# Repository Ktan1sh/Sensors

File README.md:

# Sensor Breakout Boards

These are some Sensor breakout boards I created for practicing PCB design and Git version control.

## Purpose

- Hone my Design skills
- Practice Git workflows for hardware or software projects.
- Build reusable modules for future projects.

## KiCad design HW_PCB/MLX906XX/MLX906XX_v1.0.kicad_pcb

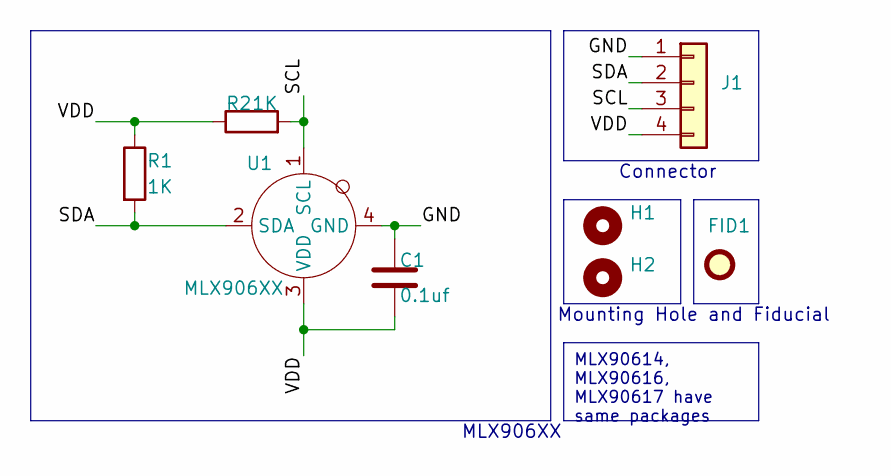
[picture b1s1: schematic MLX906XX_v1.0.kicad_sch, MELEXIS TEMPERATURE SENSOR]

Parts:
C1: 0.1uf; C_0603_1608Metric_Pad1.08x0.95mm_HandSolder
FID1: Fiducial; Fiducial_0.5mm_Mask1.5mm
H1, H2: MountingHole; MountingHole_3.2mm_M3
J1: Conn_01x04; PinSocket_1x04_P2.54mm_Horizontal
R1, R2: 1K; R_0603_1608Metric_Pad0.98x0.95mm_HandSolder
U1: MLX906XX; MLX906XX_TO39

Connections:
GND: C1.1, J1.1, U1.4 (GND)
SCL: J1.3, R2.2, U1.1 (SCL)
SDA: J1.2, R1.2, U1.2 (SDA)
VDD: C1.2, J1.4, R1.1, R2.1, U1.3 (VDD)

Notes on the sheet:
MLX90614, MLX90616, MLX90617 have same packages
Mounting Hole and Fiducial
Connector
MLX906XX

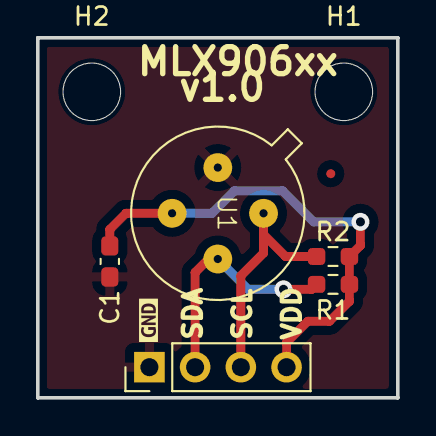
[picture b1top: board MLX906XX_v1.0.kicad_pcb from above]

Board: 2 copper layers, 20.0 x 20.0 mm, 10 parts (1 on the bottom side), 4 nets.

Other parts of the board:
kibuzzard-6799FD48, kibuzzard-6799FD48#2: G***; kibuzzard-6799FD48

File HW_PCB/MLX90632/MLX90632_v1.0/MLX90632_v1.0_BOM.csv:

"Reference","Value","Qty","DNP","MPN","Package","Description"
"C1","10n","1","","","0603","Unpolarized capacitor"
"J1","Conn_01x04","1","","","2.54 mm","Generic connector, single row, 01x04"
"R1,R2","1K","2","","","0603","Resistor"
"U1","MLX90632","1","","","5-SFN",""

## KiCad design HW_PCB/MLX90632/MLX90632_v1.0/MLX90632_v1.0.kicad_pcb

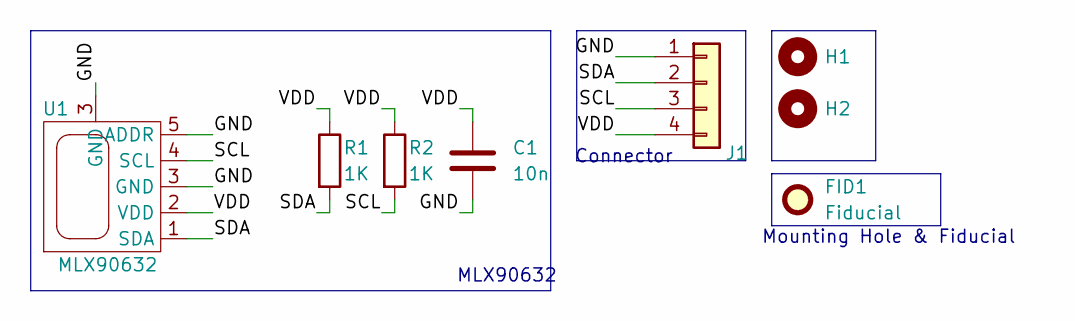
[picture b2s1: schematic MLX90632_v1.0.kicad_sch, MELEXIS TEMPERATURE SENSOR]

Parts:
C1: 10n; C_0603_1608Metric_Pad1.08x0.95mm_HandSolder
FID1: Fiducial; Fiducial_0.5mm_Mask1.5mm
H1, H2: MountingHole; MountingHole_3.2mm_M3
J1: Conn_01x04; PinHeader_1x04_P2.54mm_Vertical
R1, R2: 1K; R_0603_1608Metric_Pad0.98x0.95mm_HandSolder
U1: MLX90632; IC_MLX90632SLD-BCB-000-RE

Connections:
/GND: C1.2, J1.1, U1.3 (GND), U1.5 (ADDR)
/SCL: J1.3, R2.2, U1.4 (SCL)
/SDA: J1.2, R1.2, U1.1 (SDA)
/VDD: C1.1, J1.4, R1.1, R2.1, U1.2 (VDD)

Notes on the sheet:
MLX90632
Connector
Mounting Hole & Fiducial

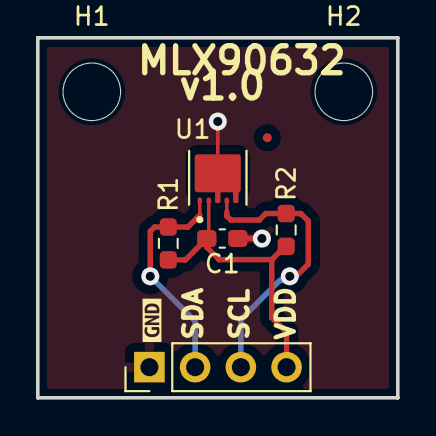
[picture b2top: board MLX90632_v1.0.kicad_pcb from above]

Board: 2 copper layers, 20.0 x 20.0 mm, 10 parts (1 on the bottom side), 4 nets.

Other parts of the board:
kibuzzard-679A3272, kibuzzard-679A3272#2: G***; kibuzzard-679A3272

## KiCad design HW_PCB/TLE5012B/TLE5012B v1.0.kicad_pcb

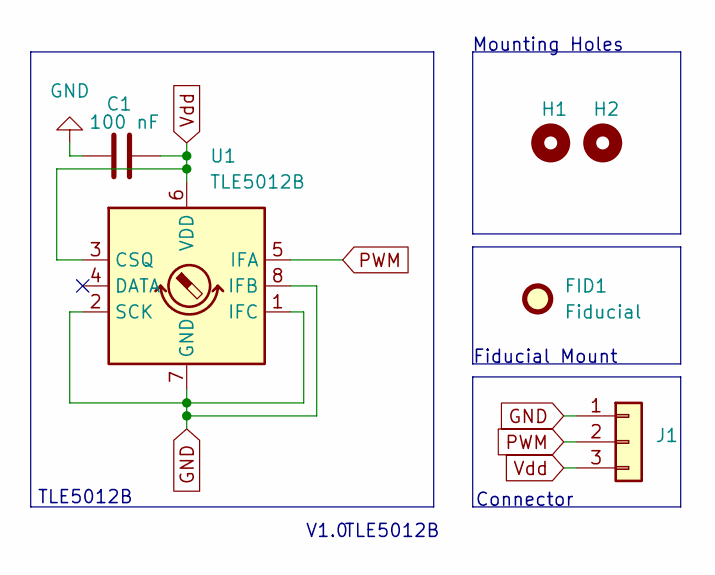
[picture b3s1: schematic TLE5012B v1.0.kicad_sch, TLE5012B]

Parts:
C1: 100 nF; C_0603_1608Metric
FID1: Fiducial; Fiducial_0.75mm_Mask2.25mm
H1, H2: MountingHole_Pad; MountingHole_3.2mm_M3
J1: PinHeader_1x03_P2.54mm_Vertical; Part Number 1-0301FBV0T
U1: TLE5012B; SOIC-8_3.9x4.9mm_P1.27mm

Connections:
GND: C1.1, J1.1, U1.1 (IFC), U1.2 (SCK), U1.7 (GND), U1.8 (IFB)
PWM: J1.2, U1.5 (IFA)
Vdd: C1.2, J1.3, U1.3 (CSQ), U1.6 (VDD)

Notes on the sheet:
TLE5012B
Mounting Holes
Connector
Fiducial Mount
V1.0

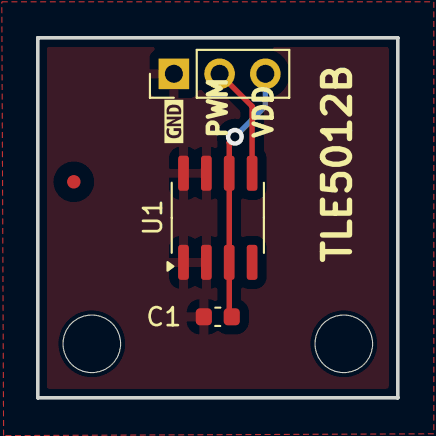
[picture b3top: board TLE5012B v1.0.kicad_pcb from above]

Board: 2 copper layers, 20.0 x 20.0 mm, 8 parts (1 on the bottom side), 3 nets.

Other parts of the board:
kibuzzard-677E552E, kibuzzard-677E552E#2: G***; kibuzzard-677E552E

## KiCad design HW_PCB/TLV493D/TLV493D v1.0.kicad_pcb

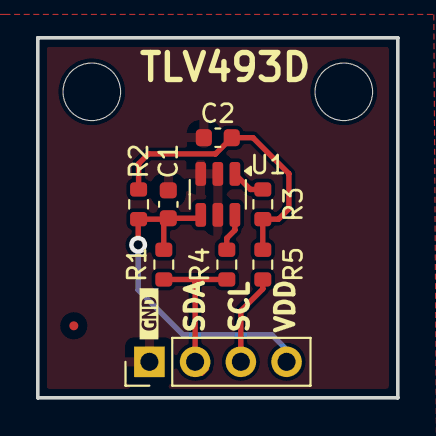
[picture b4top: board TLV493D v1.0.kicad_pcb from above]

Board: 2 copper layers, 20.0 x 20.0 mm, 14 parts (1 on the bottom side), 7 nets.

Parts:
C1: 100 nF; C_0603_1608Metric
C2: 200 pF; C_0603_1608Metric
FID2: Fiducial; Fiducial_0.5mm_Mask1.5mm
H3, H4: MountingHole_Pad; MountingHole_3.2mm_M3
J1: PinHeader_1x04_P2.54mm_Vertical
R1, R2: 1.2K; R_0603_1608Metric
R3, R4, R5: 100E; R_0603_1608Metric
U1: TLV493D; SOT-23-6
kibuzzard-67922AA7: G***; kibuzzard-67922AA7
kibuzzard-679229DC: G***; kibuzzard-679229DC

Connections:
GND: C1.2, C2.2, J1.1, U1.2 (GND), U1.3 (GND), U1.5 (GND)
unnamed: C2.1, R2.2, R3.1, R5.2
unnamed: R3.2, U1.1 (SCL/INT)
unnamed: R4.2, U1.6 (SDA/ADDR)
SCL: J1.3, R5.1
SDA: J1.2, R1.2, R4.1
Vdd: C1.1, J1.4, R1.1, R2.1, U1.4 (VDD)

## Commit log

2026-02-27 Added repo README
2026-02-27 Added ReadMe
2026-02-27 Added Read me for the Assets folder
2026-02-27 Added Symbols
2026-02-27 Added 3D models
2026-02-27 Added TLV493D sensor breakout board
2026-02-27 Added TLV493D datasheet
2026-02-27 Added MLX and TLE
2026-02-27 Added MLX Temperature Sensors
2026-02-27 Replaced some file
2026-02-27 Added datasheet
